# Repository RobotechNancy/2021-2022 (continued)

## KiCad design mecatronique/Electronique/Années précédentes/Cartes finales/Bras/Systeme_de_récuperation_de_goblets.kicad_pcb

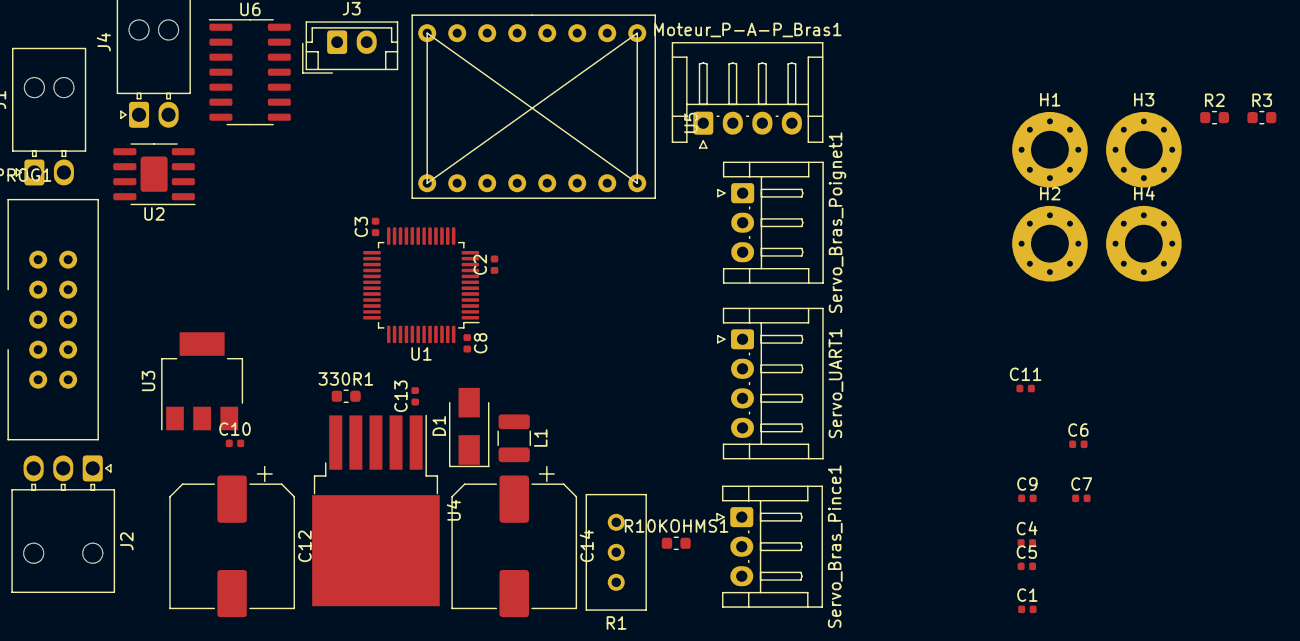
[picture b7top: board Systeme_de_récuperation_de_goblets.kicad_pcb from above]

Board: 2 copper layers, 40 parts (0 on the bottom side), 30 nets, no tracks yet.

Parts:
330R1: R_Small; R_0603_1608Metric
C1, C2, C3, C4, C5, C8, C9, C10, C11: 10 nF; C_0402_1005Metric
C6, C7: 22µF; C_0402_1005Metric
C12, C14: 220µF; CP_Elec_10x10
C13: 100 nF; C_0402_1005Metric
D1: D_Small; D_SMA
H1, H2, H3, H4: MountingHole_Pad; MountingHole_3.2mm_M3_Pad_Via
J1, J4: Bus_CAN; Molex_Nano-Fit_105313-xx02_1x02_P2.50mm_Horizontal
J2: Conn_Alim; Molex_Nano-Fit_105313-xx03_1x03_P2.50mm_Horizontal
J3: Conn_01x02_Female; JST_EH_B2B-EH-A_1x02_P2.50mm_Vertical
L1: INDUCTOR; L_1210_3225Metric
Moteur_P-A-P_Bras1: Conn_01x04_Female; JST_EH_S4B-EH_1x04_P2.50mm_Horizontal
PROG1: STM32_SW; JTAG10
R1: R_Variable; Potentiometer_Bourns_3386C_Horizontal
R2, R3: R10KOHMS; R_0603_1608Metric
R10KOHMS1: R_Small; R_0603_1608Metric
Servo_Bras_Pince1: Conn_01x03_Female; JST_EH_S3B-EH_1x03_P2.50mm_Horizontal
Servo_Bras_Poignet1: Conn_01x03_Female; JST_EH_S3B-EH_1x03_P2.50mm_Horizontal
Servo_UART1: Conn_01x04_Female; JST_EH_S4B-EH_1x04_P2.50mm_Horizontal
U1: STM32F103C8Tx; LQFP-48_7x7mm_P0.5mm
U2: TCAN337; SOIC-8-1EP_3.9x4.9mm_P1.27mm_EP2.29x3mm
U3: AMS1117-3.3; SOT-223
U4: LM2596S-ADJ; TO-263-5_TabPin3
U5: TMC2208
U6: TXB0104D; SOIC-14_3.9x8.7mm_P1.27mm

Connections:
+3V3: C2.1, C3.1, C4.1, C5.1, C7.1, C8.1, C9.1, PROG1.1, R2.1, U1.9, U1.24, U1.36, U1.48, U2.3, U3.2, U6.1
+5V: C6.1, C10.1, C11.2, J2.1, R10KOHMS1.2, Servo_Bras_Pince1.1, Servo_Bras_Poignet1.1, U3.3, U5.2, U6.8, U6.14
+12V: C12.1, C13.1, J2.3, U4.1, U5.8
+V_ADJ: C14.1, L1.2, R1.1, Servo_UART1.2
CAN_H: J1.1, J4.1, U2.7
CAN_L: J1.2, J4.2, U2.6
CAN_RX: U1.32, U2.4
CAN_TX: U1.33, U2.1
CLK: U5.11, U5.12
DIR_Moteur_P-A-P_Bras: U1.20, U6.2
Fin_De_Course_Bras: J3.2, R10KOHMS1.1, U1.27
GND: 330R1.1, C1.2, C2.2, C3.2, C4.2, C5.2, C6.2, C7.2, C8.2, C9.2, C10.2, C11.1, C12.2, C13.2, C14.2, D1.2, H1.1, H2.1, H3.1, H4.1, J2.2, J3.1, PROG1.3, PROG1.5, PROG1.9, R3.2, Servo_Bras_Pince1.2, Servo_Bras_Poignet1.2, Servo_UART1.1, U1.8, U1.23, U1.35, U1.47, U2.2, U3.1, U4.3, U4.5, U5.1, U5.7, U5.16, U6.7
H2: U5.9, U6.13
H6: U5.10, U6.12
M1A_Bras: Moteur_P-A-P_Bras1.3, U5.5
M1B_Bras: Moteur_P-A-P_Bras1.4, U5.6
M2A_Bras: Moteur_P-A-P_Bras1.2, U5.4
M2B_Bras: Moteur_P-A-P_Bras1.1, U5.3
NRST: PROG1.10, U1.7
unnamed: 330R1.2, R1.2, U4.4
unnamed: C1.1, U1.1
unnamed: D1.1, L1.1, U4.2
PWM_Pince_Bras: Servo_Bras_Pince1.3, U1.10
PWM_Poignet_Bras: Servo_Bras_Poignet1.3, U1.16
RX_Bus_UART_Coude: Servo_UART1.3, U1.12
STEP_Moteur_P-A-P_Bras: U1.29, U6.3
SWCLK: PROG1.4, R3.1, U1.38
SWDIO: PROG1.2, R2.2, U1.37
SWO: PROG1.6, U1.34
TX_Bus_UART_Coude: Servo_UART1.4, U1.13
